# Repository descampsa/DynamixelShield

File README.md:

# Dynamixel shield

## What is it?

This is an arduino shield to control dynamixel servo motors from Robotis. AX and MX series (TTL version) are supported. Thanks to their half-duplex serial control protocol, you can chain them and control a lot of motor simultaneously (up to 254 in theory). It is possible to control those motors with an arduino without additionnal hardware, but this board makes it easier and cleaner.

## How to use it?

### Hello world (aka blink my led)

First install the [ardyno](https://github.com/descampsa/ardyno/) library, using the Arduino Library Manager, or directly from the github repository.
Then open the "test_led" example and upload it. The shield can not be installed when you install the program.
Install the shield, check that the jumpers are on 'HW' position, connect the motor and a 12v power supply, and voila, the motor "led" should start blinking!
To get the motor moving (that's the point, after all), check the "test_motor" exemple. The documentation is still lacking, but by browsing examples and code, you should be able to do understand how it works. If you have any question, just ask.

### Software serial

The default mode explained above is to use the first hardware UART (Serial) of the board to communicate with the motors. This has the advantage that you can usethe full communication speed (up to 2Mbaud, by default 1Mbaud) of the protocol. However, boards that only have one hardaware uart (e.g. Uno), that means that you can't simultaneously use the USB port to communicate with the external world, since it also uses this UART. If you want to do that, you have to use the SoftwareSerial mode. The disadvantage is that you are limited to low baud rates (check the SoftwareSerial library documentation). You will have to change the baud rate of the motor using the hardware serial before (see "test_speed" example).

To use the SoftwareSerial mode, change the jumper to 'SW' position, and replace the line
```
HardwareDynamixelInterface interface(Serial,2);
```
by

```
SoftwareDynamixelInterface interface(4,3,2);
```

The first version take the hardware serial instance, and the direction pin as parameters, while the second one take rx pin, tx pin and direction pin.

### Other Hardware Serial

For boards that have multiple hardware uart, you may use any of those ports by connecting the corresponding pins to the 'EXT' connector. Just set the jumper to 'EXT ONLY' position, and connect RX/TX/DIR pins to the rx/tx pins of the uart and the direction pin configured in your code.

## Which boards are compatible?

Most of the code is platform independent, but it has only been tested with AVR boards. If you want to use another platform and find a bug, open an issue in ardyno repository.
The shield supports both 5V and 3.3V boards.

I also successfully tested it with the Arduino 101, but there are still a few shortcomings in the serial libray of this board, so this is experimental.

## Great, how do i get one?

The good news is that all is open source, the kicad project, gerber file, code, bom, all you need to make your own. Gerber and bom are also available on [kitnic](kitnic.it), where you may order the parts very easily. The bad news is that you can't buy one, i do not sell it for now.
I have a few unpopulated pcb left, however, so if you are interested, just ask and i will send you one for shipping cost.

## Warning

This board is functionnal, but has not yet been tested extensively, especially for high loads. Make sure you know what you are doing if you use it.

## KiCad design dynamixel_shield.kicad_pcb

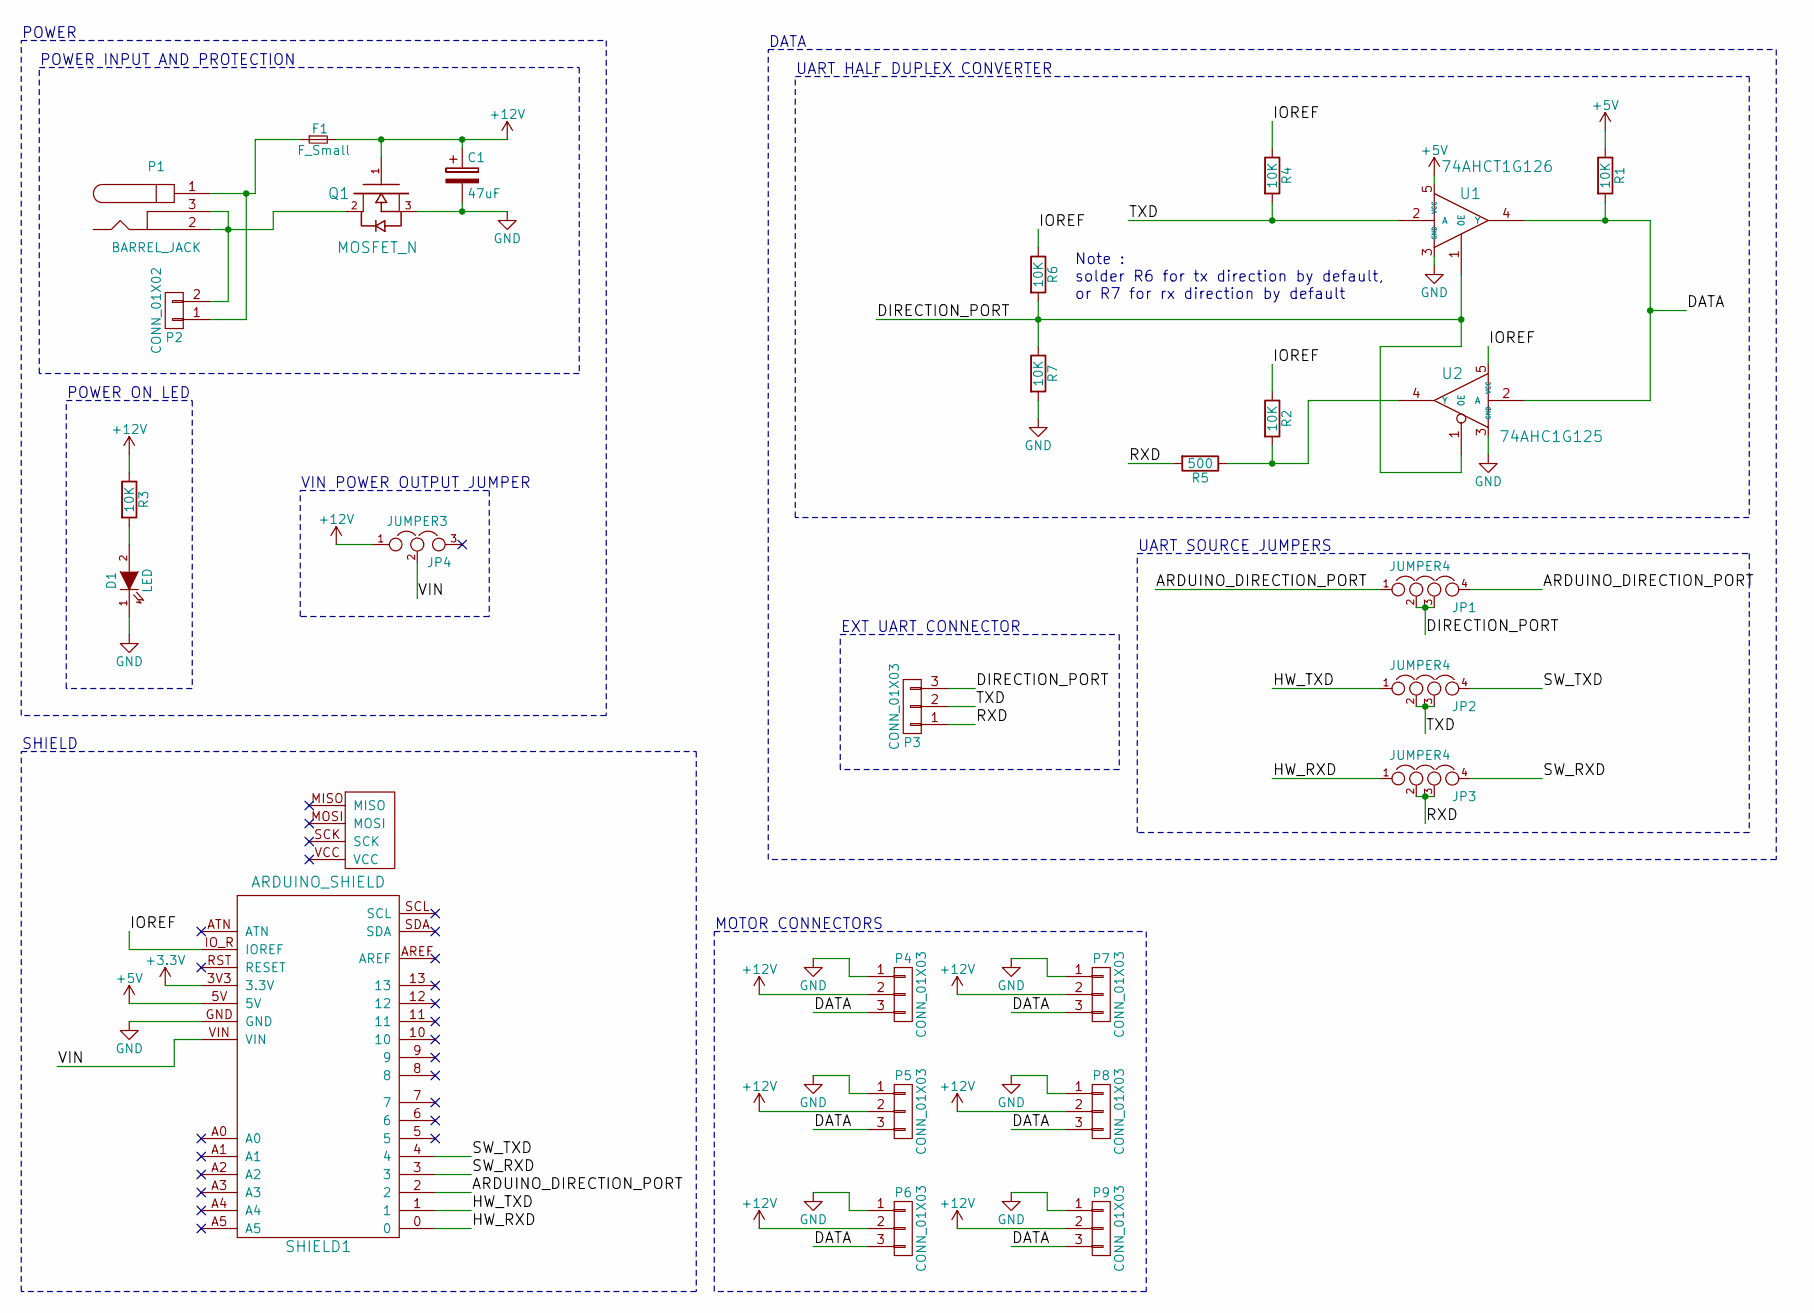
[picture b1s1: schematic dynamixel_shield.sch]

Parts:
C1: 47uF; c_elec_6.3x5.8
D1: LED; LED_0603
F1: F_Small; Fuseholder5x20_horiz_lateral
JP1, JP2, JP3: JUMPER4; Pin_Header_Straight_1x04
JP4: JUMPER3; Pin_Header_Straight_1x03
P1: BARREL_JACK
P2: CONN_01X02; bornier2
P3: CONN_01X03; Pin_Header_Angled_1x03
P4, P5, P6, P7: CONN_01X03; Molex_spox_1x3_right
P8, P9: CONN_01X03; Molex_spox_1x3_straight
Q1: MOSFET_N; TO-252-2Lead
R1, R2, R3, R4, R6, R7: 10K; R_0603_HandSoldering
R5: 500; R_0603_HandSoldering
SHIELD1: ARDUINO_SHIELD; Arduino_shield_dynamixel
U1: 74AHCT1G126; SOT-353
U2: 74AHC1G125; SOT-353

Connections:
+3V3: SHIELD1.3V3 (3.3V)
+5V: R1.1, SHIELD1.5V, U1.5 (VCC)
+12V: C1.1, F1.2, JP4.1, P4.2, P5.2, P6.2, P7.2, P8.2, P9.2, Q1.1 (G), R3.1
/ARDUINO_DIRECTION_PORT: JP1.1, JP1.4, SHIELD1.2
/DATA: P4.3, P5.3, P6.3, P7.3, P8.3, P9.3, R1.2, U1.4 (Y), U2.2 (A)
/DIRECTION_PORT: JP1.2, JP1.3, P3.3, R6.2, R7.1, U1.1 (0E), U2.1 (0E)
/HW_RXD: JP3.1, SHIELD1.0
/HW_TXD: JP2.1, SHIELD1.1
/IOREF: R2.1, R4.1, R6.1, SHIELD1.IO_R (IOREF), U2.5 (VCC)
/RXD: JP3.2, JP3.3, P3.1, R5.2
/SW_RXD: JP3.4, SHIELD1.3
/SW_TXD: JP2.4, SHIELD1.4
/TXD: JP2.2, JP2.3, P3.2, R4.2, U1.2 (A)
/VIN: JP4.2, SHIELD1.VIN
GND: C1.2, D1.1 (K), P4.1, P5.1, P6.1, P7.1, P8.1, P9.1, Q1.3 (S), R7.2, SHIELD1.GND, U1.3 (GND), U2.3 (GND)
unnamed: D1.2 (A), R3.2
unnamed: F1.1, P1.1, P2.1
unnamed: P1.2, P1.3, P2.2, Q1.2 (D)
unnamed: R2.2, R5.1, U2.4 (Y)

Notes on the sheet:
POWER INPUT AND PROTECTION
UART HALF DUPLEX CONVERTER
MOTOR CONNECTORS
POWER ON LED
SHIELD
EXT UART CONNECTOR
UART SOURCE JUMPERS
VIN POWER OUTPUT JUMPER
POWER
DATA
Note : solder R6 for tx direction by default, or R7 for rx direction by default

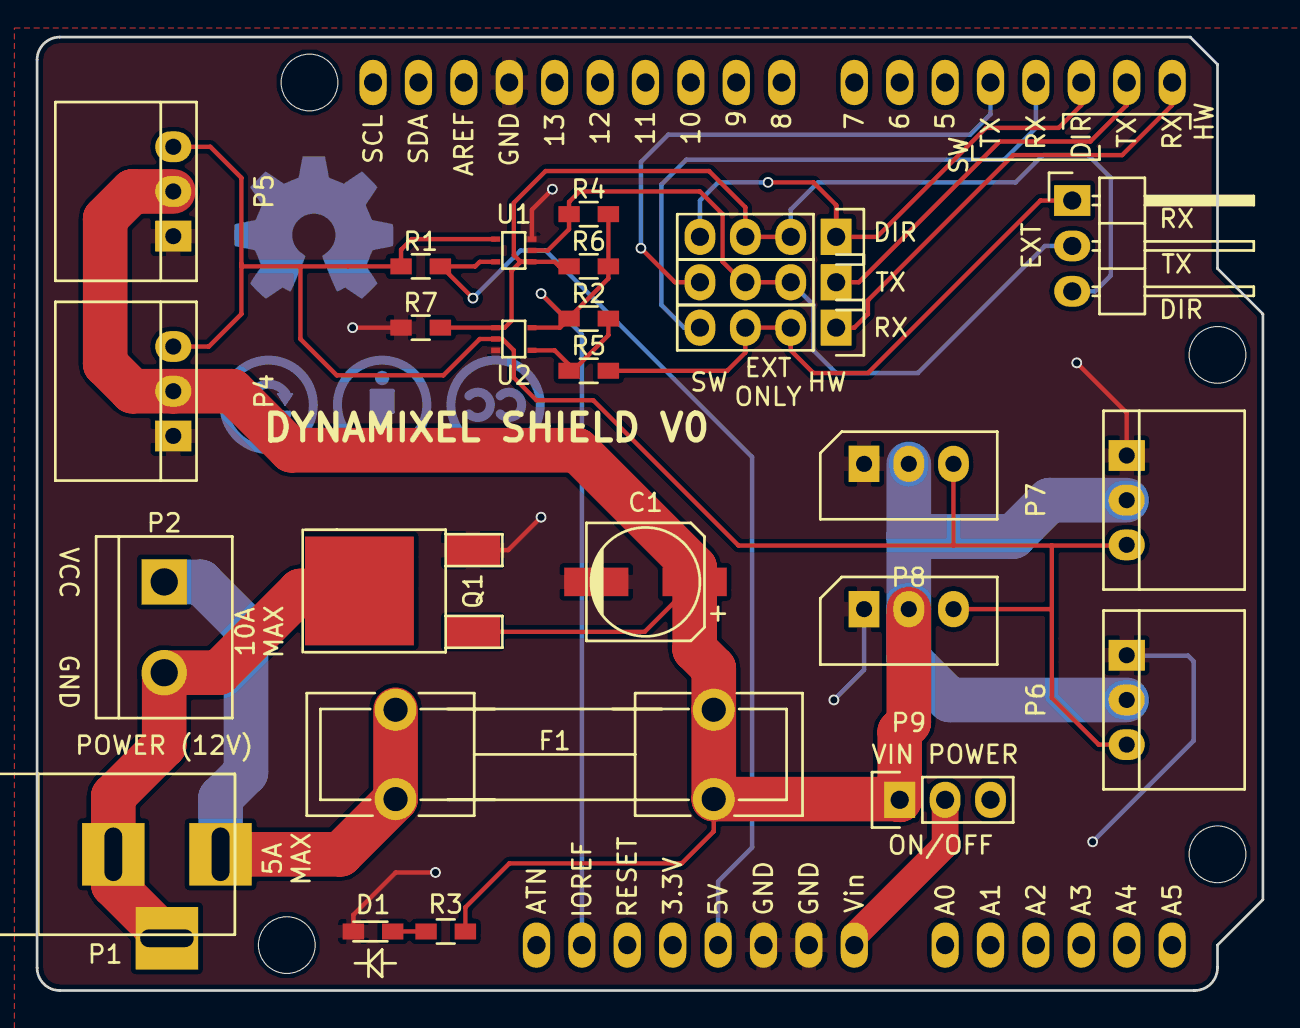
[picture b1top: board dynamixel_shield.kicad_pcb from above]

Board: 2 copper layers, 68.6 x 53.3 mm, 27 parts (0 on the bottom side), 18 nets.

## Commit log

2016-08-21 add readme and license
2016-08-24 Update silkscreen
2016-08-24 Add power on LED
2016-08-24 Fix error in schematics
    Arduino direction port was not connected in the SW configuration.
2016-08-26 move ext connector to make place for the fourth mounting hole
2016-09-07 add annotation to the schematic
2016-09-23 add bom from mouser
2016-10-01 add gerber files
2016-10-01 add 1 click bom (from mouser bom)
2016-10-01 basic description in readme
2016-10-01 add mouser number for arduino header, appears to work for digikey too
2016-10-02 complete 1-click-bom with suppliers part numbers (only mouser and digikey are sane)
2016-10-02 remove quoting, for nicer github display
2016-10-02 change capacitor height (bom related only, footprint is the same)
2016-10-02 fix description fields in 1-click_bom using kicad export script (at least it is in english now ...)
2016-10-02 update bom with more available parts
2016-10-02 remove nonsensical parts from autocomplete
2016-10-02 fix some newark part numbers
2016-10-04 add a nice README
2016-10-04 add images
2016-10-04 change images to a saner resolution
2016-10-05 small cleanup of the readme
2016-10-08 add a warning in the readme
2016-10-09 fix a few shortcomings of the pcb, thanks to tautech from eevblog forum
    remove potential acid trap between p8 and p9
    increase pad size of molex connectors
    move polarity indicators to be visible
    increase led pad size for easier soldering
2016-10-09 put the fuse before the reverse voltage protection (thanks to bktemp from eevblog forum)
    Quoting bktemp user on eevblog:
    When the fuse fails, there will be a voltage spike.
    Since there is no load except the mosfet gate, the voltage spike will damage the mosfet,
    maybe even shorting gate-source and therefore the input supply.
    If the gate is connected after the fuse, is will be connected in parallel with C1,
    providing some protection for the sensitive gate.
2016-10-10 add a few vias between ground planes (suggested by bson from eevblog)
2016-10-10 add small traces to vias, so that they are not disconnected when you refill the ground zones
2016-10-13 remove vias in ground plane
2016-10-13 add pull up and protection resistor on uart lines
2016-10-15 add optional resistor to set default direction in either rx or tx
2016-10-15 update pcb with new resistors
2016-10-15 slightly update arduino silkscreen to be visible behind headers
2016-10-15 move footprints to separate github repositories
2016-10-31 add a few vias between ground planes
2016-10-31 update resistor value
2016-10-31 update bom with new parts
2019-03-19 tweak some components placement
2019-03-20 increase capacitors, add a few vias
2019-03-20 update bom
